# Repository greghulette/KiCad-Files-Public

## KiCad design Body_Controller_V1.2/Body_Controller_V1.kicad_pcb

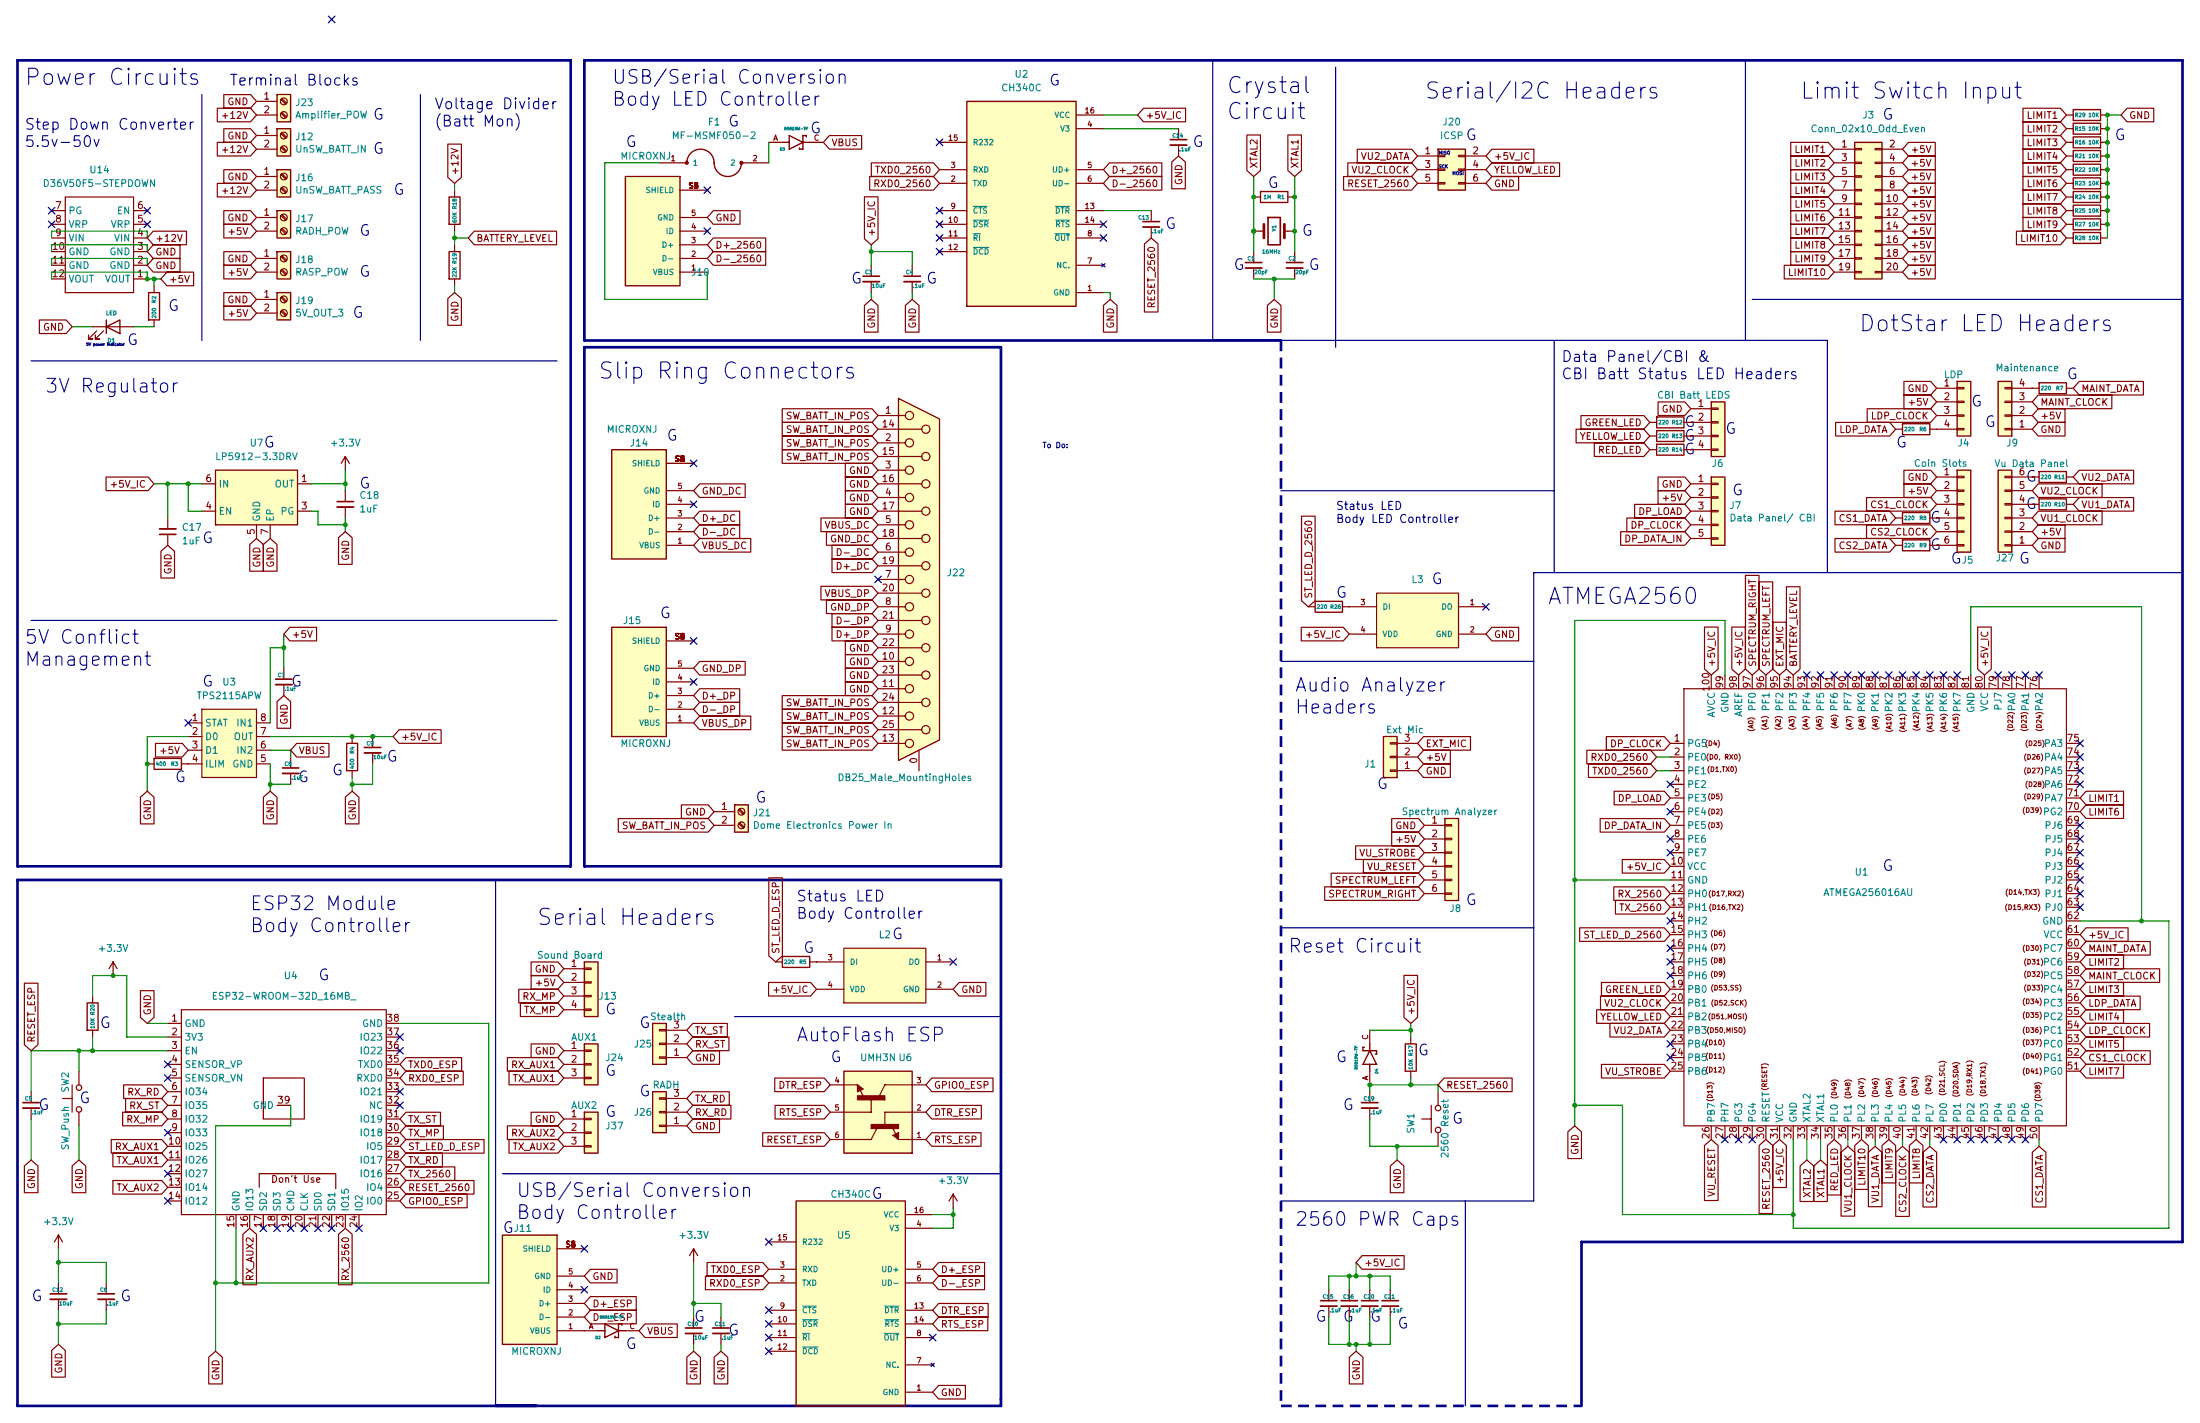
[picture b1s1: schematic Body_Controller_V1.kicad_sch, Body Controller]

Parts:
C1, C2: 20pF; C_0402_1005Metric; Mouser Part Number 81-GJM1555C1H200FB1D; LCSC C913479
C3, C9, C10, C12: 10uF; C_0402_1005Metric; Mouser Part Number 187-CL05A106MP5NUNC; LCSC C315248
C4, C5, C6, C7, C8, C11, C13, C14, C15, C16, C19, C20, C21: .1uF; C_0402_1005Metric; Mouser Part Number 187-CL05B104KB54PNC; Digikey Part Number 1276-CL05B104KB54PNCCT-ND
C17, C18: 1uF; C_0402_1005Metric; LCSC C307331
D1: LED; LED_0603_1608Metric; Mouser Part Number 859-LTST-C191KFKT; Digikey Part Number 160-1445-1-ND
D2, D3, D4: B5819W-TP; SOD3716X135N; Mouser Part Number 833-B5819W-TP; Digikey Part Number B5819W-TPMSCT-ND
F1: MF-MSMF050-2; FUSM4632X85; Mouser Part Number 652-MF-MSMF050-2; Digikey Part Number MF-MSMF050-2CT-ND
J1: Ext Mic; Molex_KK-254_AE-6410-03A_1x03_P2.54mm_Vertical; Mouser Part Number 538-22-27-2031; Digikey Part Number WM4112-ND
J3: Conn_02x10_Odd_Even; PinHeader_2x10_P2.54mm_Vertical; Mouser Part Number 649-67996-420HLF; Digikey Part Number 609-3221-ND
J4: LDP; 470531000; Mouser Part Number 538-47053-1000; LCSC C240840
J5: Coin Slots; Molex_KK-254_AE-6410-06A_1x06_P2.54mm_Vertical; Mouser Part Number 538-22-29-2061; Digikey Part Number WM2748-ND
J6: CBI Batt LEDS; 470531000; Mouser Part Number 538-47053-1000; LCSC C240840
J7: Data Panel/ CBI; Molex_KK-254_AE-6410-05A_1x05_P2.54mm_Vertical; Mouser Part Number 538-22-23-2051; LCSC C588986
J8: Spectrum Analyzer; Molex_KK-254_AE-6410-06A_1x06_P2.54mm_Vertical; Mouser Part Number 538-22-29-2061; Digikey Part Number WM2748-ND
J9: Maintenance; 470531000; Mouser Part Number 538-47053-1000; LCSC C240840
J10, J11, J14, J15: MICROXNJ; SHOUHAN_MICROXNJ; PARTREV A
J12: UnSW_BATT_IN; TerminalBlock_4Ucon_1x02_P3.50mm_Horizontal; Mouser Part Number 651-1984617; LCSC C474892
J13: Sound Board; 470531000; Mouser Part Number 538-47053-1000; LCSC C240840
J16: UnSW_BATT_PASS; TerminalBlock_4Ucon_1x02_P3.50mm_Horizontal; Mouser Part Number 651-1984617; LCSC C474892
J17: RADH_POW; TerminalBlock_4Ucon_1x02_P3.50mm_Horizontal; Mouser Part Number 651-1984617; LCSC C474892
J18: RASP_POW; TerminalBlock_4Ucon_1x02_P3.50mm_Horizontal; Mouser Part Number 651-1984617; LCSC C474892
J19: 5V_OUT_3; TerminalBlock_4Ucon_1x02_P3.50mm_Horizontal; Mouser Part Number 651-1984617; LCSC C474892
J20: ICSP; PinHeader_2x03_P2.54mm_Vertical; Mouser Part Number 649-67997-206HLF; Digikey Part Number 609-3234-ND
J21: Dome Electronics Power In; TerminalBlock_4Ucon_1x02_P3.50mm_Horizontal; Mouser Part Number 651-1984617; LCSC C474892
J22: DB25_Male_MountingHoles; DSUB-25_Male_Vertical_P2.77x2.84mm_MountingHoles; Mouser Part Number 636-171-025-103L001; Digikey Part Number 225ME-ND
J23: Amplifier_POW; TerminalBlock_4Ucon_1x02_P3.50mm_Horizontal; Mouser Part Number 651-1984617; LCSC C474892
J24: AUX1; Molex_KK-254_AE-6410-03A_1x03_P2.54mm_Vertical; Mouser Part Number 538-22-27-2031; Digikey Part Number WM4112-ND
J25: Stealth; Molex_KK-254_AE-6410-03A_1x03_P2.54mm_Vertical; Mouser Part Number 538-22-27-2031; Digikey Part Number WM4112-ND
J26: RADH; Molex_KK-254_AE-6410-03A_1x03_P2.54mm_Vertical; Mouser Part Number 538-22-27-2031; Digikey Part Number WM4112-ND
J27: Vu Data Panel; Molex_KK-254_AE-6410-06A_1x06_P2.54mm_Vertical; Mouser Part Number 538-22-29-2061; Digikey Part Number WM2748-ND
J37: AUX2; Molex_KK-254_AE-6410-03A_1x03_P2.54mm_Vertical; Mouser Part Number 538-22-27-2031; Digikey Part Number WM4112-ND
L2, L3: WS2812B-2020; Mouser Part Number 485-4684; Digikey Part Number 1528-4684-ND
R1: 1M; R_0603_1608Metric; Mouser Part Number 791-WR06X105JTL; Digikey Part Number 1292-WR06X105JTLCT-ND
R2: 200; R_0603_1608Metric; Mouser Part Number 603-RC0603JR-07200RL; Digikey Part Number 311-200GRCT-ND
R3, R4: 400; R_1206_3216Metric; Mouser Part Number 603-RT1206BRD07400RL; Digikey Part Number 13-RT1206BRD07400RLCT-ND
R5, R26: 220; R_0402_1005Metric; Mouser Part Number 603-RC0402JR-07220RL; Digikey Part Number 311-220JRCT-ND
R6, R7, R8, R9, R10, R11, R12, R13, R14: 220; R_0402_1005Metric; LCSC C352454
R15, R16, R17, R20, R21, R22, R23, R24, R25, R27, R28, R29: 10K; R_0402_1005Metric; Mouser Part Number 603-AC0402FR-0710KL; LCSC C144807
R18: 60K; R_Axial_DIN0204_L3.6mm_D1.6mm_P5.08mm_Horizontal
R19: 22K; R_Axial_DIN0204_L3.6mm_D1.6mm_P5.08mm_Horizontal
SW1: 2560 Reset; TS-1101-C-W; LCSC C318938
SW2: SW_Push; TS-1101-C-W; LCSC C318938
U1: ATMEGA256016AU; QFP50P1600X1600X120-100N; Mouser Part Number 556-ATMEGA2560-16AU; LCSC C22460
U2, U5: CH340C; SOIC127P600X180-16N; PARTREV 2G; LCSC C84681
U3: TPS2115APW; TSSOP-8_4.4x3mm_P0.65mm; Mouser Part Number 595-TPS2115APW; Digikey Part Number 296-26918-5-ND
U4: ESP32-WROOM-32D_16MB_; ESP32-WROOM-32; Mouser Part Number 356-ES32WROOM32D16MB; Digikey Part Number 1965-ESP32-WROOM-32D-N16CT-ND
U6: UMH3N; UMT6; Mouser Part Number 755-UMH3NTN; Digikey Part Number 4617-UMH3NTR-ND
U7: LP5912-3.3DRV; WSON-6-1EP_2x2mm_P0.65mm_EP1x1.6mm_ThermalVias; Mouser Part Number 595-LP5912-3.3DRVR; Digikey Part Number 296-47214-1-ND
U14: D36V50F5-STEPDOWN
Y1: 16MHz; XTAL_HC49P488W46L1150T500H350; LCSC C279575

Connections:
+3V3: C6.1, C10.1, C11.1, C12.1, C18.1, R20.1, U4.2 (3V3), U5.4 (V3), U5.16 (VCC), U7.1 (OUT)
+5V: C7.1, J1.2, J3.2, J3.4, J3.6, J3.8, J3.10, J3.12, J3.14, J3.16, J3.18, J3.20, J4.2, J5.2, J7.2, J8.2, J9.2, J13.2, J17.2, J18.2, J19.2, J27.2, R2.1, U3.3 (D1), U3.8 (IN1), U14.1 (VOUT), U14.12 (VOUT)
+5V_IC: C3.1, C4.1, C9.1, C15.1, C16.1, C17.2, C20.1, C21.1, D4.C, J20.2, L2.4 (VDD), L3.4 (VDD), R4.1, R17.1, U1.10 (VCC), U1.31 (VCC), U1.61 (VCC), U1.80 (VCC), U1.98 (AREF), U1.100 (AVCC), U2.16 (VCC), U3.7 (OUT), U7.4 (EN), U7.6 (IN)
+12V: J12.2, J16.2, J23.2, R18.1, U14.4 (VIN), U14.9 (VIN)
BATTERY_LEVEL: R18.2, R19.1, U1.94 (PF3)
CS1_CLOCK: J5.3, U1.52 (PG1)
CS1_DATA: R8.2, U1.50 (PD7)
CS2_CLOCK: J5.5, U1.40 (PL5)
CS2_DATA: R9.2, U1.42 (PL7)
D+_2560: J10.3 (D+), U2.5 (UD+)
D+_DC: J14.3 (D+), J22.19
D+_DP: J15.3 (D+), J22.9
D+_ESP: J11.3 (D+), U5.5 (UD+)
D-_2560: J10.2 (D-), U2.6 (UD-)
D-_DC: J14.2 (D-), J22.6
D-_DP: J15.2 (D-), J22.21
D-_ESP: J11.2 (D-), U5.6 (UD-)
DP_CLOCK: J7.4, U1.1 (PG5)
DP_DATA_IN: J7.5, U1.7 (PE5)
DP_LOAD: J7.3, U1.5 (PE3)
DTR_ESP: U5.13 (~DTR), U6.2, U6.4
EXT_MIC: J1.3, U1.95 (PF2)
GND: C1.2, C2.2, C3.2, C4.2, C5.2, C6.2, C7.2, C8.2, C9.2, C10.2, C11.2, C12.2, C14.2, C15.2, C16.2, C17.1, C18.2, C19.2, C20.2, C21.2, D1.1 (K), J1.1, J4.1, J5.1, J6.1, J7.1, J8.1, J9.1, J10.5 (GND), J11.5 (GND), J12.1, J13.1, J16.1, J17.1, J18.1, J19.1, J20.6, J21.1, J22.3, J22.4, J22.10, J22.11, J22.16, J22.17, J22.22, J22.23, J23.1, J24.1, J25.1, J26.1, J27.1, J37.1, L2.2 (GND), L3.2 (GND), R3.2, R4.2, R15.2, R16.2, R19.2, R21.2, R22.2, R23.2, R24.2, R25.2, R27.2, R28.2, R29.2, SW1.1, SW2.1, U1.11 (GND), U1.32 (GND), U1.62 (GND), U1.81 (GND), U1.99 (GND), U2.1 (GND), U3.2 (D0), U3.5 (GND), U4.1 (GND), U4.15 (GND), U4.38 (GND), U4.39 (GND), U5.1 (GND), U7.3 (PG), U7.5 (GND), U7.7 (EP), U14.2 (GND), U14.3 (GND), U14.10 (GND), U14.11 (GND)
GND_DC: J14.5 (GND), J22.18
GND_DP: J15.5 (GND), J22.8
GPIO0_ESP: U4.25 (IO0), U6.3
GREEN_LED: R12.2, U1.19 (PB0)
LDP_CLOCK: J4.3, U1.54 (PC1)
LDP_DATA: R6.2, U1.56 (PC3)
LIMIT1: J3.1, R29.1, U1.71 (PA7)
LIMIT2: J3.3, R15.1, U1.59 (PC6)
LIMIT3: J3.5, R16.1, U1.57 (PC4)
LIMIT4: J3.7, R21.1, U1.55 (PC2)
LIMIT5: J3.9, R22.1, U1.53 (PC0)
LIMIT6: J3.11, R23.1, U1.70 (PG2)
LIMIT7: J3.13, R24.1, U1.51 (PG0)
LIMIT8: J3.15, R25.1, U1.41 (PL6)
LIMIT9: J3.17, R27.1, U1.39 (PL4)
LIMIT10: J3.19, R28.1, U1.37 (PL2)
MAINT_CLOCK: J9.3, U1.58 (PC5)
MAINT_DATA: R7.1, U1.60 (PC7)
unnamed: C13.1, U2.13 (~DTR)
unnamed: C14.1, U2.4 (V3)
unnamed: D1.2 (A), R2.2
unnamed: D2.A, J11.1 (VBUS)
unnamed: D3.A, F1.2
unnamed: F1.1, J10.1 (VBUS)
unnamed: J4.4, R6.1
unnamed: J5.4, R8.1
unnamed: J5.6, R9.1
unnamed: J6.2, R12.1
unnamed: J6.3, R13.1
unnamed: J6.4, R14.1
unnamed: J9.4, R7.2
unnamed: J27.4, R10.2
unnamed: J27.6, R11.2
unnamed: L2.3 (DI), R5.1
unnamed: L3.3 (DI), R26.1
unnamed: R3.1, U3.4 (ILIM)
RED_LED: R14.2, U1.35 (PL0)
RESET_2560: C13.2, C19.1, D4.A, J20.5, R17.2, SW1.2, U1.30 (RESET), U4.26 (IO4)
RESET_ESP: C5.1, R20.2, SW2.2, U4.3 (EN), U6.6
RTS_ESP: U5.14 (~RTS), U6.1, U6.5
RXD0_2560: U1.2 (PE0), U2.2 (TXD)
RXD0_ESP: U4.34 (RXD0), U5.2 (TXD)
RX_2560: U1.12 (PH0), U4.23 (IO15)
RX_AUX1: J24.2, U4.10 (IO25)
RX_AUX2: J37.2, U4.16 (IO13)
RX_MP: J13.3, U4.8 (IO32)
RX_RD: J26.2, U4.6 (IO34)
RX_ST: J25.2, U4.7 (IO35)
SPECTRUM_LEFT: J8.5, U1.96 (PF1)
SPECTRUM_RIGHT: J8.6, U1.97 (PF0)
ST_LED_D_2560: R26.2, U1.15 (PH3)
ST_LED_D_ESP: R5.2, U4.29 (IO5)
SW_BATT_IN_POS: J21.2, J22.1, J22.2, J22.12, J22.13, J22.14, J22.15, J22.24, J22.25
TXD0_2560: U1.3 (PE1), U2.3 (RXD)
TXD0_ESP: U4.35 (TXD0), U5.3 (RXD)
TX_2560: U1.13 (PH1), U4.27 (IO16)
TX_AUX1: J24.3, U4.11 (IO26)
TX_AUX2: J37.3, U4.13 (IO14)
TX_MP: J13.4, U4.30 (IO18)
TX_RD: J26.3, U4.28 (IO17)
TX_ST: J25.3, U4.31 (IO19)
VBUS: C8.1, D2.C, D3.C, U3.6 (IN2)
VBUS_DC: J14.1 (VBUS), J22.5
VBUS_DP: J15.1 (VBUS), J22.20
VU1_CLOCK: J27.3, U1.36 (PL1)
VU1_DATA: R10.1, U1.38 (PL3)
VU2_CLOCK: J20.3, J27.5, U1.20 (PB1)
VU2_DATA: J20.1, R11.1, U1.22 (PB3)
VU_RESET: J8.4, U1.26 (PB7)
VU_STROBE: J8.3, U1.25 (PB6)
XTAL1: C2.1, R1.1, U1.34 (XTAL1), Y1.2
XTAL2: C1.1, R1.2, U1.33 (XTAL2), Y1.1
YELLOW_LED: J20.4, R13.2, U1.21 (PB2)

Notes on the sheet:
MISO
Status LED Body Controller
Limit Switch Input
ESP32 Module Body Controller
Serial/I2C Headers
Voltage Divider (Batt Mon)
3V Regulator
Slip Ring Connectors
2560 PWR Caps
Power Circuits
Step Down Converter 5.5v-50v
AutoFlash ESP
Crystal Circuit
5V power indicator
Status LED Body LED Controller
USB/Serial Conversion Body Controller
SCK
MOSI
Reset Circuit
Data Panel/CBI & CBI Batt Status LED Headers
ATMEGA2560
5V Conflict Management
DotStar LED Headers
Audio Analyzer Headers
To Do:
USB/Serial Conversion Body LED Controller
Serial Headers
Terminal Blocks

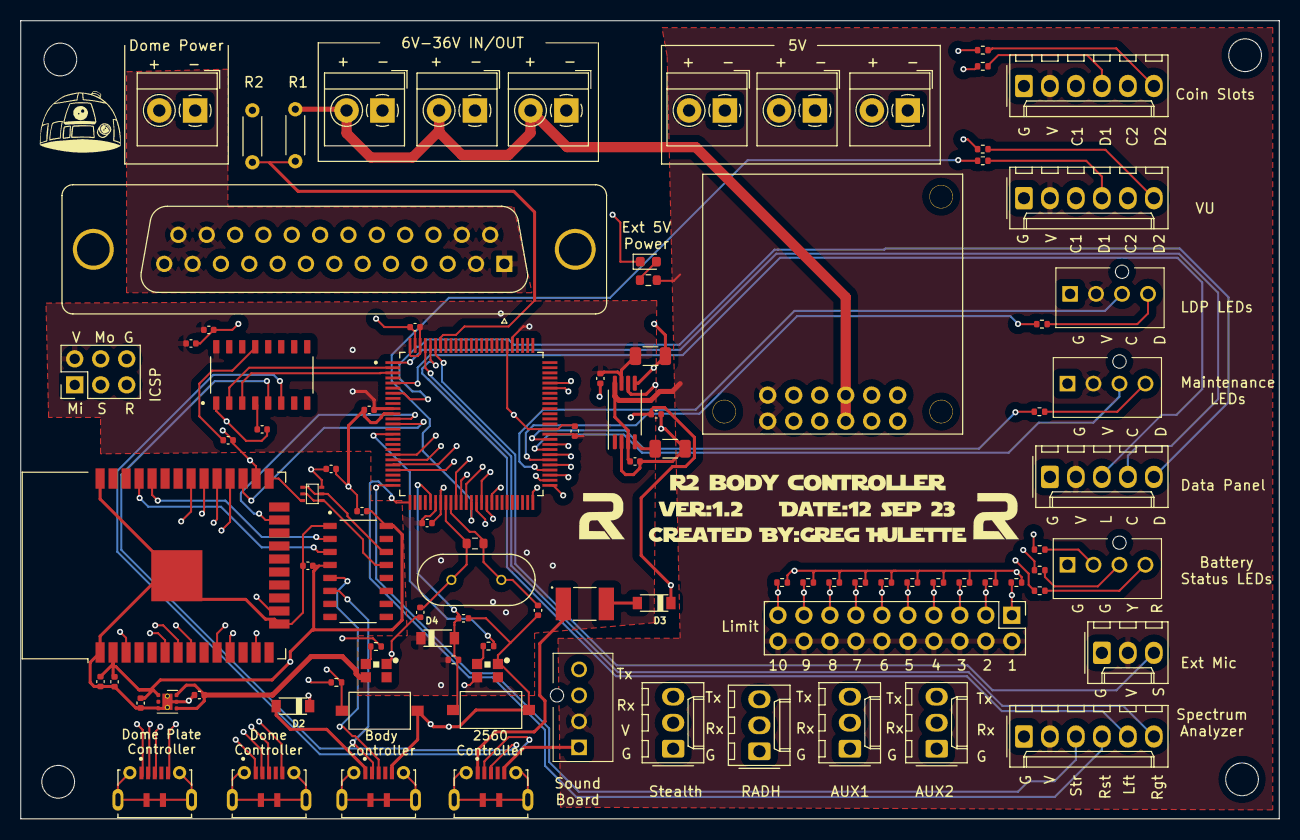
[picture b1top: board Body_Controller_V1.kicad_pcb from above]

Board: 4 copper layers, 123.0 x 78.0 mm, 95 parts (0 on the bottom side), 96 nets.

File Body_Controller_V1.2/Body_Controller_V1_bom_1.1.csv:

Component,Description,Part,References,Value,Footprint,Quantity Per PCB,Datasheet,Digikey Part Number,LCSC,Manufacturer,Manufacturer's Part Number,Mouser Part Number,MANUFACTURER,MAXIMUM_PACKAGE_HEIGHT,PARTREV,STANDARD
1,"Unpolarized capacitor, small symbol",C_Small,C1 C2,20pF,C_0402_1005Metric,2,https://search.murata.co.jp/Ceramy/image/img/A01X/G101/ENG/G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,490-11204-1-ND,C913479,Murata Electronics,GJM1555C1H200FB01D,81-GJM1555C1H200FB1D,,,,
2,"Unpolarized capacitor, small symbol",C_Small,C4 C5 C6 C7 C8 C11 C13 C14 C15 C16 C19 C20 C21,.1uF,C_0402_1005Metric,13,https://www.samsungsem.com/resources/file/global/support/pro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,1276-CL05B104KB54PNCCT-ND,C307331,Samsung Electro-Mechanics,CL05B104KB54PNC,187-CL05B104KB54PNC,,,,
3,"Unpolarized capacitor, small symbol",C_Small,C17 C18,1uF,C_0402_1005Metric,2,https://datasheet.lcsc.com/lcsc/1810191222_Samsung-Electro-M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,,C307331,,,,,,,
4,"Unpolarized capacitor, small symbol",C_Small,C3 C9 C10 C12,10uF,C_0402_1005Metric,4,https://media.digikey.com/pdf/Data%20Sheets/Samsung%20PDFs/C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,1276-1450-1-ND,C315248,Samsung Electro-Mechanics,CL05A106MP5NUNC,187-CL05A106MP5NUNC,,,,
5,,B5819W-TP_1,D2 D3 D4,B5819W-TP,SOD3716X135N,3,https://www.mccsemi.com/pdf/Products/B5817W-B5819W(SOD-123).pdf ,B5819W-TPMSCT-ND,C84354,Micro Commercial Components,B5819W-TP,833-B5819W-TP,Micro Commercial Components,,,
6,Light emitting diode,LED,D1,LED,LED_0603_1608Metric,1,https://optoelectronics.liteon.com/upload/download/DS22-2000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,160-1445-1-ND,C160478,Lite-On Inc.,LTST-C191KFKT,859-LTST-C191KFKT,,,,
7,,MF-MSMF050-2,F1,MF-MSMF050-2,FUSM4632X85,1,https://datasheet.lcsc.com/lcsc/1811061740_BOURNS-MF-MSMF050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,MF-MSMF050-2CT-ND,C17313,Bourns,MF-MSMF050-2,652-MF-MSMF050-2,Bourns,,,
8,USB Micro Type B connector,USB_B_Micro,J10 J11 J14 J15,2560 USB,USB_Micro-B_Amphenol_10118194_Horizontal,4,https://datasheet.lcsc.com/lcsc/1811131822_Amphenol-ICC-1011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,609-4618-1-ND,C132563,Amphenol ICC (FCI),10118194-0001LF,649-10118194-0001LF,,,,
9,"Generic connector, single row, 01x06, script generated (kicad-library-utils/schlib/autogen/connector/)",Conn_01x06,J5 J8 J27,Coin Slots,Molex_KK-254_AE-6410-06A_1x06_P2.54mm_Vertical,3,https://www.molex.com/pdm_docs/sd/022292061_sd.pdf,WM2748-ND,C587046,Molex,0022292061,538-22-29-2061,,,,
10,"Generic connector, double row, 02x10, odd/even pin numbering scheme (row 1 odd numbers, row 2 even numbers), script generated (kicad-library-utils/schlib/autogen/connector/)",Conn_02x10_Odd_Even,J3,Conn_02x10_Odd_Even,PinHeader_2x10_P2.54mm_Vertical,1,https://cdn.amphenol-cs.com/media/wysiwyg/files/drawing/67996.pdf,609-3221-ND,C492427,Amphenol ICC (FCI),67996-420HLF,649-67996-420HLF,,,,
11,"Generic connector, single row, 01x05, script generated (kicad-library-utils/schlib/autogen/connector/)",Conn_01x05,J7,Data Panel/ CBI,Molex_KK-254_AE-6410-05A_1x05_P2.54mm_Vertical,1,https://www.molex.com/pdm_docs/sd/022232051_sd.pdf,WM4203-ND,C588986,Molex,538-22-23-2051,538-22-23-2051,,,,
12,"Generic connector, single row, 01x03, script generated (kicad-library-utils/schlib/autogen/connector/)",Conn_01x03,J1 J24 J25 J26 J37,Ext Mic,Molex_KK-254_AE-6410-03A_1x03_P2.54mm_Vertical,5,https://www.molex.com/pdm_docs/sd/022272031_sd.pdf,WM4112-ND,C471416,Molex,0022272031,538-22-27-2031,,,,
13,"Generic connector, double row, 02x03, odd/even pin numbering scheme (row 1 odd numbers, row 2 even numbers), script generated (kicad-library-utils/schlib/autogen/connector/)",Conn_02x03_Odd_Even,J20,ICSP,PinHeader_2x03_P2.54mm_Vertical,1,https://cdn.amphenol-cs.com/media/wysiwyg/files/drawing/67996.pdf,609-3234-ND,C236051,Amphenol ICC (FCI),67997-206HLF,649-67997-206HLF,,,,
14,"Generic connector, single row, 01x04, script generated (kicad-library-utils/schlib/autogen/connector/)",Conn_01x04,J4 J6 J9 J13,LDP,470531000,4,https://datasheet.lcsc.com/lcsc/1811051309_MOLEX-470531000_C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,WM4330-ND,C240840,Molex,0470531000,538-47053-1000,,,,
15,"Generic screw terminal, single row, 01x02, script generated (kicad-library-utils/schlib/autogen/connector/)",Screw_Terminal_01x02,J12 J16 J17 J18 J19 J21 J23,UnSW_BATT_IN,TerminalBlock_4Ucon_1x02_P3.50mm_Horizontal,7,https://datasheet.lcsc.com/lcsc/2001160007_Cixi-Kefa-Elec-KF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,277-1721-ND,C474892,Phoenix Contact,1984617,651-1984617,,,,
16,,WS2812B-2020,L2 L3,WS2812B-2020,WS2812B-2020,2,https://datasheet.lcsc.com/lcsc/2012110135_Worldsemi-WS2812B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,1528-4684-ND,C965555,Worldsemi,WS2812B-2020,485-4684,,,,
17,Resistor,R,R2,200,R_0603_1608Metric,1,https://www.yageo.com/upload/media/product/productsearch/dat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,311-200GRCT-ND,C114686,YAGEO,RC0603JR-07200RL,603-RC0603JR-07200RL,,,,
18,Resistor,R,R5 R6 R7 R8 R9 R10 R11 R12 R13 R14 R26,220,R_0402_1005Metric,11,https://www.yageo.com/upload/media/product/productsearch/dat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,311-220JRCT-ND,C137899 C352454,YAGEO,RC0402JR-07220RL,603-RC0402JR-07220RL,,,,
19,Resistor,R,R3 R4,400,R_1206_3216Metric,2,https://www.yageo.com/upload/media/product/productsearch/dat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,13-RT1206BRD07400RLCT-ND,C706413,YAGEO,RT1206BRD07400RL,603-RT1206BRD07400RL,,,,
20,Resistor,R,R15 R16 R17 R20 R21 R22 R23 R24 R25 R27 R28 R29,10K,R_0402_1005Metric,12,https://www.yageo.com/upload/media/product/productsearch/dat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,YAG3436CT-ND,C144807,YAGEO,AC0402FR-0710KL,603-AC0402FR-0710KL,,,,
21,Resistor,R,R19,22K,R_Axial_DIN0204_L3.6mm_D1.6mm_P5.08mm_Horizontal,1,https://www.seielect.com/Catalog/SEI-RMCF_RMCP.pdf,,,,,,,,,
22,Resistor,R,R18,60K,R_Axial_DIN0204_L3.6mm_D1.6mm_P5.08mm_Horizontal,1,https://www.yageo.com/upload/media/product/productsearch/dat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,,,YAGEO,,,,,,
23,Resistor,R,R1,1M,R_0603_1608Metric,1,http://www.passivecomponent.com/wp-content/uploads/chipR/ASC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,1292-WR06X105JTLCT-ND,C384292,Walsin Tech Corp,WR06X105 JTL,791-WR06X105JTL,,,,
24,"Push button switch, generic, two pins",SW_Push,SW1,2560 Reset,GT-TC057A-H050-L1,1,https://datasheet.lcsc.com/lcsc/2110111130_XKB-Connectivity-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,EG2529CT-ND,C2886915,E-Switch,TL3302BF180QG/TR,,,,,
25,"Push button switch, generic, two pins",SW_Push,SW2,SW_Push,GT-TC057A-H050-L1,1,https://datasheet.lcsc.com/lcsc/2110111130_XKB-Connectivity-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,EG2529CT-ND,C2886915,E-Switch,TL3302BF180QG/TR,,,,,
26,,ATMEGA256016AU,U1,ATMEGA256016AU,QFP50P1600X1600X120-100N,1,https://datasheet.lcsc.com/lcsc/1809041913_Microchip-Tech-AT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,ATMEGA2560-16AU-ND,C22460,Microchip Technology,ATMEGA2560-16AU,556-ATMEGA2560-16AU,,,,
27,,CH340C,U2 U5,CH340C,SOIC127P600X180-16N,2,https://datasheet.lcsc.com/lcsc/2008191806_WCH-Jiangsu-Qin-H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,,C84681,WCH,CH340C,,WCH,1.8 mm,2G,IPC 7351B
28,,D36V50F5-STEPDOWN,U14,D36V50F5-STEPDOWN,D36V50F5-STEPDOWN,1,,,,,,,,,,
29,,ESP32-WROOM-32-Custom,U4,ESP32-WROOM-32D_16MB_,ESP32-WROOM-32,1,https://datasheet.lcsc.com/lcsc/2005211207_Espressif-Systems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,1965-ESP32-WROOM-32D-N16CT-ND,C529578,Espressif Systems,ESP32-WROOM-32D-N16,356-ES32WROOM32D16MB,,,,
30,"500-mA Ultra-Low-Noise Low-IQ LDO, 3.3V, WSON-6",LP5912-3.3DRV,U7,LP5912-3.3DRV,WSON-6-1EP_2x2mm_P0.65mm_EP1x1.6mm_ThermalVias,1,http://www.ti.com/lit/ds/symlink/lp5912.pdf,296-47214-1-ND,C524780,Texas Instruments,LP5912-3.3DRVR,595-LP5912-3.3DRVR,,,,
31,,TPS2115APW,U3,TPS2115APW,TSSOP-8_4.4x3mm_P0.65mm,1,https://www.ti.com/general/docs/suppproductinfo.tsp?distId=1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,296-26918-5-ND,C70287,Texas Instruments,TPS2115APW,595-TPS2115APW,,,,
32,,UMH3N,U6,UMH3N,UMT6,1,https://datasheet.lcsc.com/lcsc/1809211024_Jiangsu-Changjing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,4617-UMH3NTR-ND,C62892,Yangjie Technology,UMH3N,755-UMH3NTN,,,,
33,Two pin crystal,Crystal,Y1,16MHz,XTAL_HC49P488W46L1150T500H350,1,https://datasheet.lcsc.com/lcsc/1912111437_ECEC-ZheJiang-E-a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,,C279575,ECEC(ZheJiang E ast Crystal Elec),B16000J114,,,,,





Component Groups:,33
Component Count:,94
Fitted Components:,94
Number of PCBs:,1
Total components:,94
Schematic Version:,1.1
Schematic Date:,2023-02-10
PCB Variant:,default
BoM Date:,"Tuesday, September 12, 2023 at 02:32:41 PM"
Schematic Source:,Body_Controller_V1.kicad_sch
KiCad Version:,Eeschema (6.0.0-0)

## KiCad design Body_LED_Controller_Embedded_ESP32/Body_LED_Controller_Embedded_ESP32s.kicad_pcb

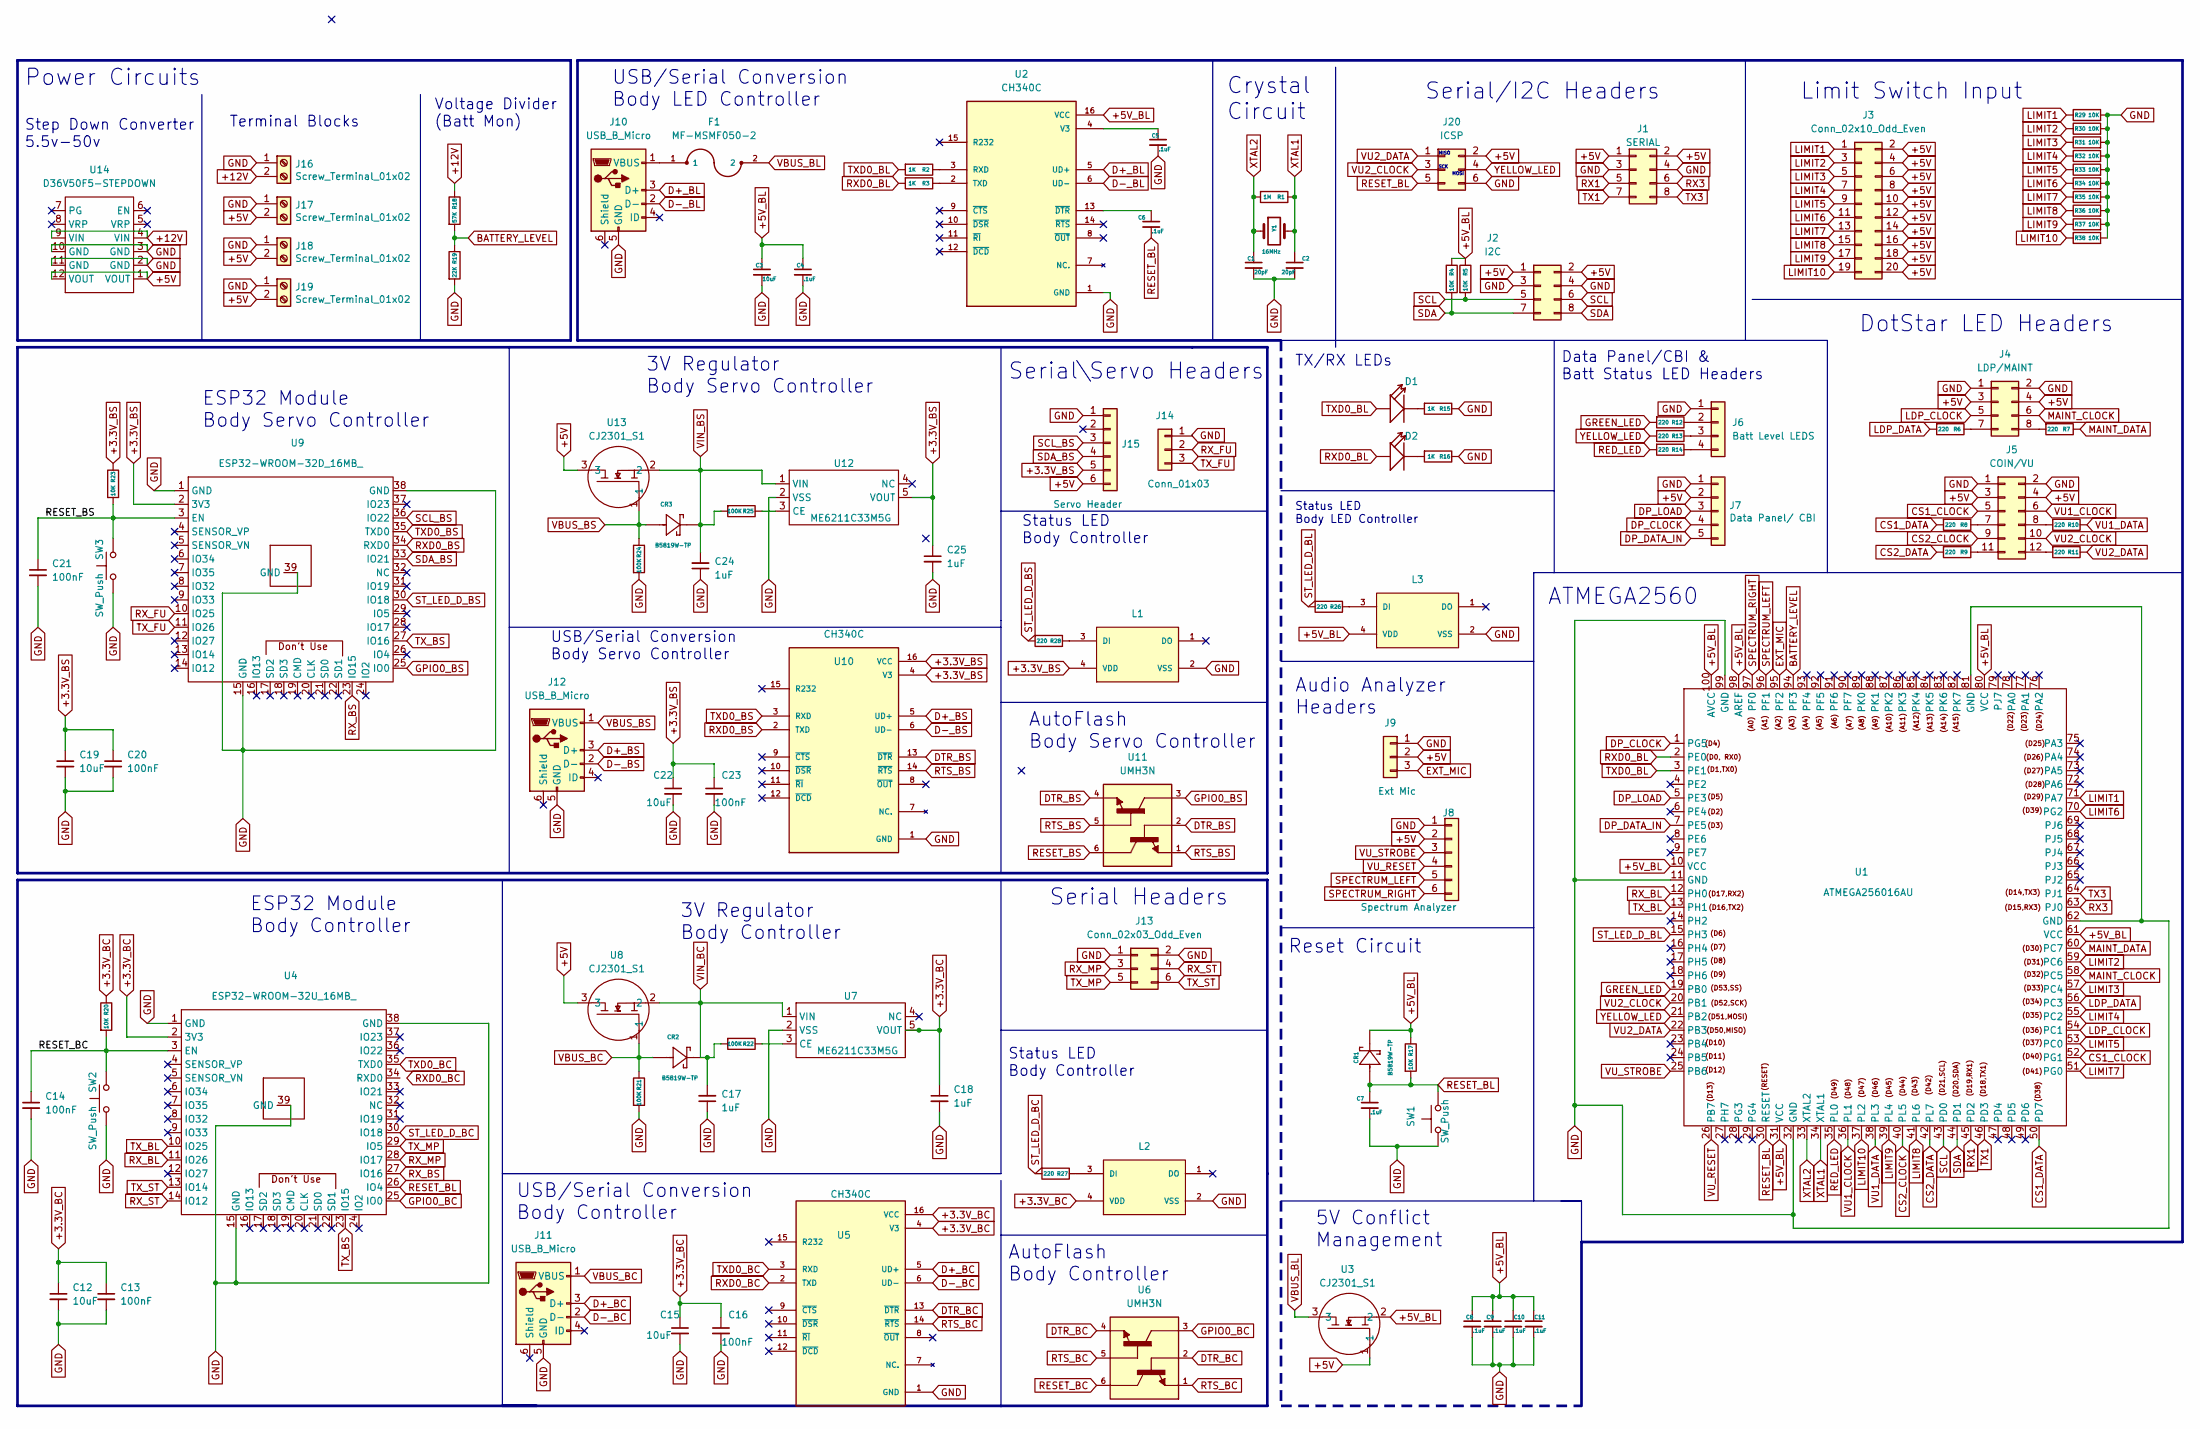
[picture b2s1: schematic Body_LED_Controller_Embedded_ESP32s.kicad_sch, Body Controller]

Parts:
C1, C2: 20pF; C_0402_1005Metric; LCSC C1554
C3, C12, C15, C19, C22: 10uF; C_0402_1005Metric; LCSC C315248
C4, C5, C6, C7, C8, C9, C10, C11: .1uF; C_0402_1005Metric; LCSC C307331
C13, C14, C16, C20, C21: 100nF; C_0402_1005Metric; LCSC C307331
C17, C18, C24, C25: 1uF; C_0402_1005Metric; LCSC C307331
C23: 100nF; C_0402_1005Metric
CR1: B5819W-TP; SOD3716X135N; LCSC C84354
CR2, CR3: B5819W-TP; SOD3716X135N
D1, D2: SMD-LED-CLEAR-BLUE(0402); LED-0402; MPN BL-HB337A-AV-TRB; LCSC C130724
F1: MF-MSMF050-2; FUSM4632X85; LCSC C17313
J1: SERIAL; PinHeader_2x04_P2.54mm_Vertical; LCSC C225519
J2: I2C; PinHeader_2x04_P2.54mm_Vertical; LCSC C225519
J3: Conn_02x10_Odd_Even; PinHeader_2x10_P2.54mm_Vertical; LCSC C492427
J4: LDP/MAINT; PinHeader_2x04_P2.54mm_Vertical; LCSC C225519
J5: COIN/VU; PinHeader_2x06_P2.54mm_Vertical; LCSC C225521
J6: Batt Level LEDS; PinHeader_1x04_P2.54mm_Vertical; LCSC C390680
J7: Data Panel/ CBI; PinHeader_1x05_P2.54mm_Vertical; LCSC C390682
J8: Spectrum Analyzer; PinHeader_1x06_P2.54mm_Vertical; LCSC C190819
J9: Ext Mic; PinHeader_1x03_P2.54mm_Vertical; LCSC C390679
J10, J11, J12: USB_B_Micro; USB_Micro-B_Amphenol_10118194_Horizontal; LCSC C132563
J13: Conn_02x03_Odd_Even; PinHeader_2x03_P2.54mm_Vertical; LCSC C390690
J14: Conn_01x03; PinHeader_1x03_P2.54mm_Vertical; LCSC C390679
J15: Servo Header; PinHeader_1x06_P2.54mm_Vertical; LCSC C190819
J16, J17, J18, J19: Screw_Terminal_01x02; TerminalBlock_4Ucon_1x02_P3.50mm_Horizontal; LCSC C474892
J20: ICSP; PinHeader_2x03_P2.54mm_Vertical; LCSC C390690
L1, L2, L3: WS2812B-2020; LCSC C965555
R1: 1M; R_0603_1608Metric; LCSC C328343
R2, R3, R15, R16: 1K; R_0402_1005Metric; LCSC C478866
R4, R5, R29, R30, R31, R32, R33, R34, R35, R36, R37, R38: 10K; R_0402_1005Metric; LCSC C269674
R6, R7, R8, R9, R10, R11, R12, R13, R14, R26: 220; R_0402_1005Metric; LCSC C352454
R17: 10K; R_0603_1608Metric; LCSC C269701
R18: 57K; R_0603_1608Metric; LCSC C245983
R19: 22K; R_0603_1608Metric; LCSC C325646
R20, R23: 10K; R_0603_1608Metric; LCSC C190321
R21, R22, R24, R25: 100K; R_0603_1608Metric; LCSC C365065
R27, R28: 220; R_0402_1005Metric
SW1, SW2, SW3: SW_Push; GT-TC057A-H050-L1; LCSC C692465
U1: ATMEGA256016AU; QFP50P1600X1600X120-100N; LCSC C22460
U2, U5, U10: CH340C; SOIC127P600X180-16N; PARTREV 2G; LCSC C82942
U3, U8, U13: CJ2301_S1; SOT-23; LCSC C8547
U4: ESP32-WROOM-32U_16MB_; ESP32-WROOM-32U; LCSC C529580
U6, U11: UMH3N; UMT6; LCSC C62892
U7, U12: ME6211C33M5G; SOT-23-5; LCSC C82942
U9: ESP32-WROOM-32D_16MB_; ESP32-WROOM-32; LCSC C529578
U14: D36V50F5-STEPDOWN
Y1: 16MHz; XTAL_HC49P488W46L1150T500H350; LCSC C279575

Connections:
+3.3V_BC: C12.1, C13.1, C15.1, C16.1, C18.1, L2.4 (VDD), R20.1, U4.2 (3V3), U5.4 (V3), U5.16 (VCC), U7.5 (VOUT)
+3.3V_BS: C19.1, C20.1, C22.1, C23.1, C25.1, J15.5, L1.4 (VDD), R23.1, U9.2 (3V3), U10.4 (V3), U10.16 (VCC), U12.5 (VOUT)
+5V: J1.1, J1.2, J2.1, J2.2, J3.2, J3.4, J3.6, J3.8, J3.10, J3.12, J3.14, J3.16, J3.18, J3.20, J4.3, J4.4, J5.3, J5.4, J7.2, J8.2, J9.2, J15.6, J17.2, J18.2, J19.2, J20.2, U3.1, U8.3, U13.3, U14.1 (VOUT), U14.12 (VOUT)
+5V_BL: C3.1, C4.1, C8.1, C9.1, C10.1, C11.1, CR1.C, L3.4 (VDD), R4.1, R5.1, R17.1, U1.10 (VCC), U1.31 (VCC), U1.61 (VCC), U1.80 (VCC), U1.98 (AREF), U1.100 (AVCC), U2.16 (VCC), U3.2
+12V: J16.2, R18.1, U14.4 (VIN), U14.9 (VIN)
BATTERY_LEVEL: R18.2, R19.1, U1.94 (PF3)
CS1_CLOCK: J5.5, U1.52 (PG1)
CS1_DATA: R8.2, U1.50 (PD7)
CS2_CLOCK: J5.9, U1.40 (PL5)
CS2_DATA: R9.2, U1.42 (PL7)
D+_BC: J11.3 (D+), U5.5 (UD+)
D+_BL: J10.3 (D+), U2.5 (UD+)
D+_BS: J12.3 (D+), U10.5 (UD+)
D-_BC: J11.2 (D-), U5.6 (UD-)
D-_BL: J10.2 (D-), U2.6 (UD-)
D-_BS: J12.2 (D-), U10.6 (UD-)
DP_CLOCK: J7.4, U1.1 (PG5)
DP_DATA_IN: J7.5, U1.7 (PE5)
DP_LOAD: J7.3, U1.5 (PE3)
DTR_BC: U5.13 (~DTR), U6.2, U6.4
DTR_BS: U10.13 (~DTR), U11.2, U11.4
EXT_MIC: J9.3, U1.95 (PF2)
GND: C1.2, C2.2, C3.2, C4.2, C5.2, C7.2, C8.2, C9.2, C10.2, C11.2, C12.2, C13.2, C14.2, C15.2, C16.2, C17.1, C18.2, C19.2, C20.2, C21.2, C22.2, C23.2, C24.1, C25.2, J1.3, J1.4, J2.3, J2.4, J4.1, J4.2, J5.1, J5.2, J6.1, J7.1, J8.1, J9.1, J10.5 (GND), J11.5 (GND), J12.5 (GND), J13.1, J13.2, J14.1, J15.1, J16.1, J17.1, J18.1, J19.1, J20.6, L1.2 (VSS), L2.2 (VSS), L3.2 (VSS), R15.1, R16.1, R19.2, R21.2, R24.2, R29.2, R30.2, R31.2, R32.2, R33.2, R34.2, R35.2, R36.2, R37.2, R38.2, SW1.1, SW2.1, SW3.1, U1.11 (GND), U1.32 (GND), U1.62 (GND), U1.81 (GND), U1.99 (GND), U2.1 (GND), U4.1 (GND), U4.15 (GND), U4.38 (GND), U4.39 (GND), U5.1 (GND), U7.2 (VSS), U9.1 (GND), U9.15 (GND), U9.38 (GND), U9.39 (GND), U10.1 (GND), U12.2 (VSS), U14.2 (GND), U14.3 (GND), U14.10 (GND), U14.11 (GND)
GPIO0_BC: U4.25 (IO0), U6.3
GPIO0_BS: U9.25 (IO0), U11.3
GREEN_LED: R12.2, U1.19 (PB0)
LDP_CLOCK: J4.5, U1.54 (PC1)
LDP_DATA: R6.2, U1.56 (PC3)
LIMIT1: J3.1, R29.1, U1.71 (PA7)
LIMIT2: J3.3, R30.1, U1.59 (PC6)
LIMIT3: J3.5, R31.1, U1.57 (PC4)
LIMIT4: J3.7, R32.1, U1.55 (PC2)
LIMIT5: J3.9, R33.1, U1.53 (PC0)
LIMIT6: J3.11, R34.1, U1.70 (PG2)
LIMIT7: J3.13, R35.1, U1.51 (PG0)
LIMIT8: J3.15, R36.1, U1.41 (PL6)
LIMIT9: J3.17, R37.1, U1.39 (PL4)
LIMIT10: J3.19, R38.1, U1.37 (PL2)
MAINT_CLOCK: J4.6, U1.58 (PC5)
MAINT_DATA: R7.1, U1.60 (PC7)
unnamed: C5.1, U2.4 (V3)
unnamed: C6.1, U2.13 (~DTR)
unnamed: D1.-, R15.2
unnamed: D2.-, R16.2
unnamed: F1.1, J10.1 (VBUS)
unnamed: J4.7, R6.1
unnamed: J4.8, R7.2
unnamed: J5.7, R8.1
unnamed: J5.8, R10.2
unnamed: J5.11, R9.1
unnamed: J5.12, R11.2
unnamed: J6.2, R12.1
unnamed: J6.3, R13.1
unnamed: J6.4, R14.1
unnamed: L1.3 (DI), R28.1
unnamed: L2.3 (DI), R27.1
unnamed: L3.3 (DI), R26.1
unnamed: R2.1, U2.3 (RXD)
unnamed: R3.1, U2.2 (TXD)
unnamed: R22.1, U7.3 (CE)
unnamed: R25.1, U12.3 (CE)
RED_LED: R14.2, U1.35 (PL0)
RESET_BC: C14.1, R20.2, SW2.2, U4.3 (EN), U6.6
RESET_BL: C6.2, C7.1, CR1.A, J20.5, R17.2, SW1.2, U1.30 (RESET), U4.26 (IO4)
RESET_BS: C21.1, R23.2, SW3.2, U9.3 (EN), U11.6
RTS_BC: U5.14 (~RTS), U6.1, U6.5
RTS_BS: U10.14 (~RTS), U11.1, U11.5
RX1: J1.5, U1.45 (PD2)
RX3: J1.6, U1.63 (PJ0)
RXD0_BC: U5.2 (TXD)
RXD0_BL: D2.+, R3.2, U1.2 (PE0)
RXD0_BS: U9.34 (RXD0), U10.2 (TXD)
RX_BL: U1.12 (PH0), U4.11 (IO26)
RX_BS: U4.27 (IO16), U9.23 (IO15)
RX_FU: J14.2, U9.10 (IO25)
RX_MP: J13.3, U4.28 (IO17)
RX_ST: J13.4, U4.14 (IO12)
SCL: J2.5, J2.6, R5.2, U1.43 (PD0)
SCL_BS: J15.3, U9.36 (IO22)
SDA: J2.7, J2.8, R4.2, U1.44 (PD1)
SDA_BS: J15.4, U9.33 (IO21)
SPECTRUM_LEFT: J8.5, U1.96 (PF1)
SPECTRUM_RIGHT: J8.6, U1.97 (PF0)
ST_LED_D_BC: R27.2, U4.30 (IO18)
ST_LED_D_BL: R26.2, U1.15 (PH3)
ST_LED_D_BS: R28.2, U9.30 (IO18)
TX1: J1.7, U1.46 (PD3)
TX3: J1.8, U1.64 (PJ1)
TXD0_BC: U4.35 (TXD0), U5.3 (RXD)
TXD0_BL: D1.+, R2.2, U1.3 (PE1)
TXD0_BS: U9.35 (TXD0), U10.3 (RXD)
TX_BL: U1.13 (PH1), U4.10 (IO25)
TX_BS: U4.23 (IO15), U9.27 (IO16)
TX_FU: J14.3, U9.11 (IO26)
TX_MP: J13.5, U4.29 (IO5)
TX_ST: J13.6, U4.13 (IO14)
VBUS_BC: CR2.A, J11.1 (VBUS), R21.1, U8.1
VBUS_BL: F1.2, U3.3
VBUS_BS: CR3.A, J12.1 (VBUS), R24.1, U13.1
VIN_BC: C17.2, CR2.C, R22.2, U7.1 (VIN), U8.2
VIN_BS: C24.2, CR3.C, R25.2, U12.1 (VIN), U13.2
VU1_CLOCK: J5.6, U1.36 (PL1)
VU1_DATA: R10.1, U1.38 (PL3)
VU2_CLOCK: J5.10, J20.3, U1.20 (PB1)
VU2_DATA: J20.1, R11.1, U1.22 (PB3)
VU_RESET: J8.4, U1.26 (PB7)
VU_STROBE: J8.3, U1.25 (PB6)
XTAL1: C2.1, R1.1, U1.34 (XTAL1), Y1.2
XTAL2: C1.1, R1.2, U1.33 (XTAL2), Y1.1
YELLOW_LED: J20.4, R13.2, U1.21 (PB2)

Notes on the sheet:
MISO
Status LED Body Controller
Limit Switch Input
ESP32 Module Body Controller
3V Regulator Body Servo Controller
Serial/I2C Headers
USB/Serial Conversion Body Servo Controller
Voltage Divider (Batt Mon)
3V Regulator Body Controller
Serial\Servo Headers
Power Circuits
Step Down Converter 5.5v-50v
AutoFlash Body Controller
Crystal Circuit
AutoFlash Body Servo Controller
Status LED Body LED Controller
USB/Serial Conversion Body Controller
SCK
MOSI
Reset Circuit
TX/RX LEDs
Data Panel/CBI & Batt Status LED Headers
ATMEGA2560
5V Conflict Management
ESP32 Module Body Servo Controller
DotStar LED Headers
Audio Analyzer Headers
USB/Serial Conversion Body LED Controller
Serial Headers
Terminal Blocks
